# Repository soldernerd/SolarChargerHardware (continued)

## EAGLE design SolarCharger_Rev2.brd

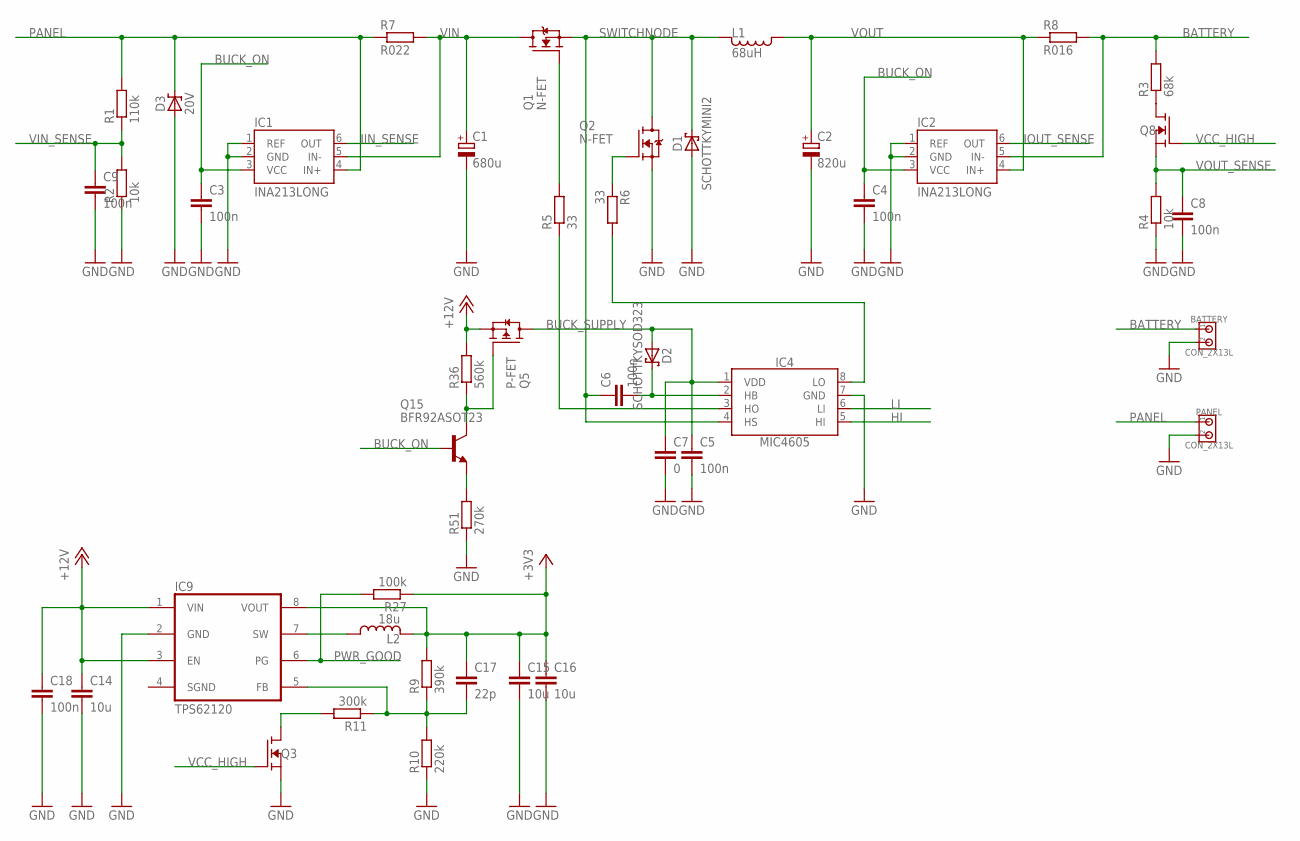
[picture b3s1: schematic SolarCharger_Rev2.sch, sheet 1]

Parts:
BATTERY: CON_2X13L; 200MIL_2X
C1: 680u; 10MM
C2: 820u; 10MM
C3, C4, C5, C6, C8, C9: 100n; C0805
C7: 0; C0805
C14: 10u; C1206
C15, C16: 10u; C0805
C17: 22p; C0805
C18: 100n; C1206
D1: SCHOTTKYMINI2; MINI2-F3-B
D2: SCHOTTKYSOD323; SOD323
D3: 20V; SMC
IC1, IC2: INA213LONG; SC70-6_LONG
IC4: MIC4605; SOIC8
IC9: TPS62120; SOT-23-8
L1: 68uH; MSS1583
L2: 18u; LPS3015
PANEL: CON_2X13L; 200MIL_2X
Q1, Q2: N-FET; TO263-3
Q3, Q8: N-FETSOT23; SOT23
Q5: P-FET; SOT23
Q15: BFR92ASOT23; SOT23
R1: 110k; R0805
R2, R4: 10k; R0805
R3: 68k; R0805
R5, R6: 33; R0805
R7: R022; 0612
R8: R016; 0612
R9: 390k; R0805
R10: 220k; R0805
R11: 300k; R0805
R27: 100k; R0805
R36: 560k; R0805
R51: 270k; R0805

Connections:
BATTERY: BATTERY.1, IC2.5 (IN-), R3.2, R8.2; also elsewhere on the board
BUCK_ON: C3.1, C4.1, IC1.3 (VCC), IC2.3 (VCC), Q15.1 (B); also elsewhere on the board
BUCK_SUPPLY: C5.1, C7.1, D2.A, IC4.1 (VDD), Q5.3 (D)
GND: BATTERY.2, C1.-, C2.-, C3.2, C4.2, C5.2, C7.2, C8.2, C9.2, C14.2, C15.2, C16.2, C18.2, D1.A, D3.A, IC1.1 (REF), IC1.2 (GND), IC2.1 (REF), IC2.2 (GND), IC4.7 (GND), IC9.2 (GND), PANEL.2, Q2.3 (S), Q3.2 (S), R2.1, R4.1, R10.1, R51.1; also elsewhere on the board
HI: IC4.5 (HI); also elsewhere on the board
IIN_SENSE: IC1.6 (OUT); also elsewhere on the board
IOUT_SENSE: IC2.6 (OUT); also elsewhere on the board
LI: IC4.6 (LI); also elsewhere on the board
unnamed: C6.2, D2.C, IC4.2 (HB)
unnamed: Q1.1 (G), R5.2
unnamed: Q3.3 (D), R11.2
unnamed: Q2.1 (G), R6.1
unnamed: IC4.8 (LO), R6.2
unnamed: IC9.7 (SW), L2.1
unnamed: C17.2, IC9.5 (FB), R9.1, R10.2, R11.1
unnamed: IC4.3 (HO), R5.1
unnamed: Q5.1 (G), Q15.3 (C), R36.1
unnamed: Q8.3 (D), R3.1
unnamed: Q15.2 (E), R51.2
PANEL: D3.C, IC1.4 (IN+), PANEL.1, R1.2, R7.1
PWR_GOOD: IC9.6 (PG), R27.2; also elsewhere on the board
SWITCHNODE: C6.1, D1.C, IC4.4 (HS), L1.2, Q1.3 (S), Q2.TAB (D)
VCC: C15.1, C16.1, C17.1, IC9.8 (VOUT), L2.2, R9.2, R27.1; also elsewhere on the board
VCC_HIGH: Q3.1 (G), Q8.1 (G); also elsewhere on the board
VIN: C1.+, IC1.5 (IN-), Q1.TAB (D), R7.2
VIN_SENSE: C9.1, R1.1, R2.2; also elsewhere on the board
VOUT: C2.+, C14.1, C18.1, IC2.4 (IN+), IC9.1 (VIN), IC9.3 (EN), L1.1, Q5.2 (S), R8.1, R36.2; also elsewhere on the board
VOUT_SENSE: C8.1, Q8.2 (S), R4.2; also elsewhere on the board

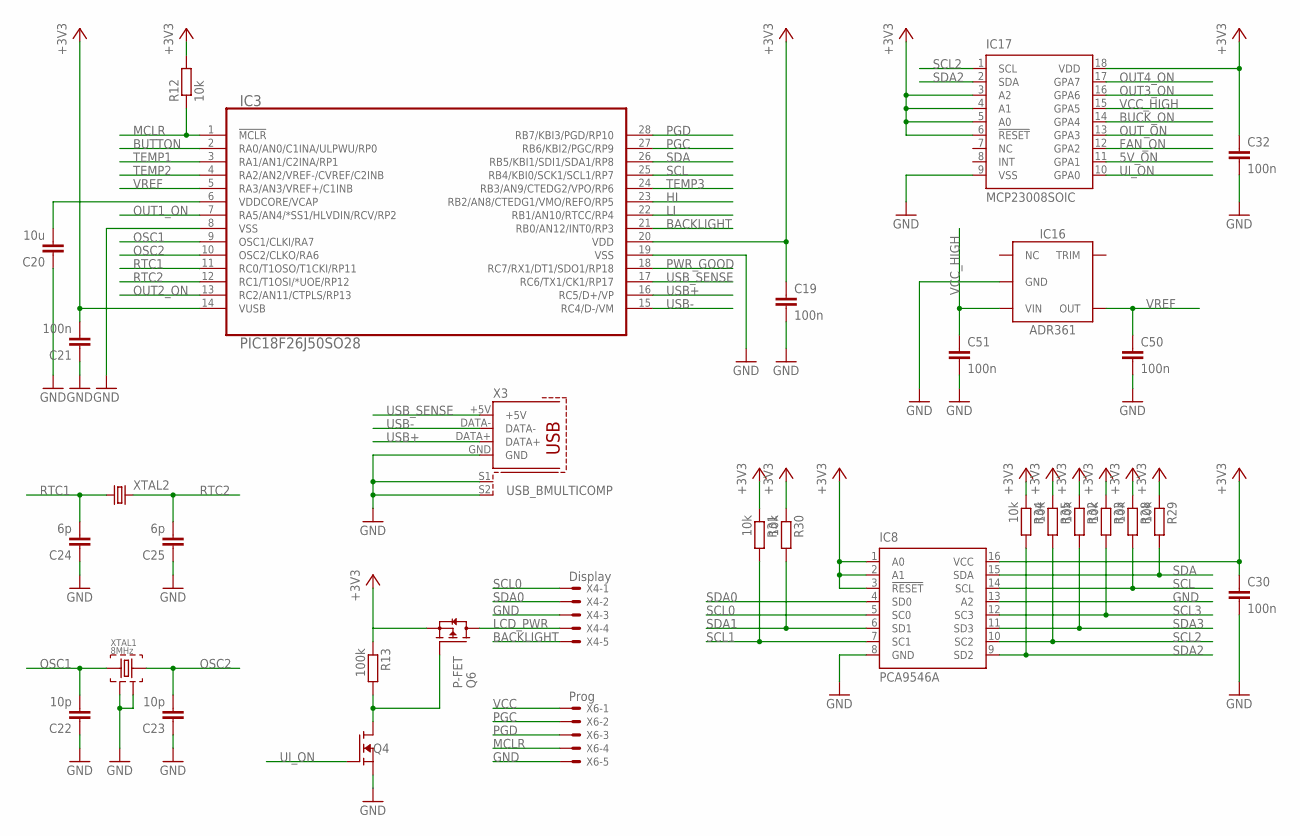
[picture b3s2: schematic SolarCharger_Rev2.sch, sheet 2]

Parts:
C19, C21, C30, C32, C50, C51: 100n; C0805
C20: 10u; C0805
C22, C23: 10p; C0805
C24, C25: 6p; C0805
IC3: PIC18F26J50SO28; SO28W
IC8: PCA9546A; SO16
IC16: ADR361; SOT23-5
IC17: MCP23008SOIC; SO18W
Q4: N-FETSOT23; SOT23
Q6: P-FET; SOT23
R12, R28, R29, R30, R31, R32, R33, R34, R35: 10k; R0805
R13: 100k; R0805
X3: USB_BMULTICOMP; USB_B
X4: Display; 22-23-2051
X6: Prog; 22-23-2051
XTAL1: 8MHz; 5X3.2MM
XTAL2: CRYSTAL3.2X1.5; 3.2X1.5MM

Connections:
5V_ON: IC17.11 (GPA1); also elsewhere on the board
BACKLIGHT: IC3.21 (RB0/AN12/INT0/RP3), X4.5
BUCK_ON: IC17.14 (GPA4); also elsewhere on the board
BUTTON: IC3.2 (RA0/AN0/C1INA/ULPWU/RP0); also elsewhere on the board
FAN_ON: IC17.12 (GPA2); also elsewhere on the board
GND: C19.2, C20.1, C21.1, C22.1, C23.1, C24.1, C25.1, C30.2, C32.2, C50.2, C51.2, IC3.8 (VSS), IC3.19 (VSS), IC8.8 (GND), IC8.13 (A2), IC16.2 (GND), IC17.9 (VSS), Q4.2 (S), X3.GND, X3.S1, X3.S2, X4.3, X6.5, XTAL1.2, XTAL1.4; also elsewhere on the board
HI: IC3.23 (RB2/AN8/CTEDG1/VMO/REFO/RP5); also elsewhere on the board
LCD_PWR: Q6.3 (D), X4.4
LI: IC3.22 (RB1/AN10/RTCC/RP4); also elsewhere on the board
MCLR: IC3.1 (!MCLR!), R12.1, X6.4
unnamed: Q4.3 (D), Q6.1 (G), R13.2
unnamed: C20.2, IC3.6 (VDDCORE/VCAP)
OSC1: C22.2, IC3.9 (OSC1/CLKI/RA7), XTAL1.1
OSC2: C23.2, IC3.10 (OSC2/CLKO/RA6), XTAL1.3
OUT1_ON: IC3.7 (RA5/AN4/*SS1/HLVDIN/RCV/RP2); also elsewhere on the board
OUT2_ON: IC3.13 (RC2/AN11/CTPLS/RP13); also elsewhere on the board
OUT3_ON: IC17.16 (GPA6); also elsewhere on the board
OUT4_ON: IC17.17 (GPA7); also elsewhere on the board
OUT_ON: IC17.13 (GPA3); also elsewhere on the board
PGC: IC3.27 (RB6/KBI2/PGC/RP9), X6.2; also elsewhere on the board
PGD: IC3.28 (RB7/KBI3/PGD/RP10), X6.3; also elsewhere on the board
PWR_GOOD: IC3.18 (RC7/RX1/DT1/SDO1/RP18); also elsewhere on the board
RTC1: C24.2, IC3.11 (RC0/T1OSO/T1CKI/RP11), XTAL2.1
RTC2: C25.2, IC3.12 (RC1/T1OSI/*UOE/RP12), XTAL2.2
SCL: IC3.25 (RB4/KBI0/SCK1/SCL1/RP7), IC8.14 (SCL), R28.2
SCL0: IC8.5 (SC0), X4.1
SCL1: IC8.7 (SC1), R31.2; also elsewhere on the board
SCL2: IC8.10 (SC2), IC17.1 (SCL), R35.2
SCL3: IC8.12 (SC3), R33.2; also elsewhere on the board
SDA: IC3.26 (RB5/KBI1/SDI1/SDA1/RP8), IC8.15 (SDA), R29.2
SDA0: IC8.4 (SD0), X4.2
SDA1: IC8.6 (SD1), R30.2; also elsewhere on the board
SDA2: IC8.9 (SD2), IC17.2 (SDA), R34.2
SDA3: IC8.11 (SD3), R32.2; also elsewhere on the board
TEMP1: IC3.3 (RA1/AN1/C2INA/RP1); also elsewhere on the board
TEMP2: IC3.4 (RA2/AN2/VREF-/CVREF/C2INB); also elsewhere on the board
TEMP3: IC3.24 (RB3/AN9/CTEDG2/VPO/RP6); also elsewhere on the board
UI_ON: IC17.10 (GPA0), Q4.1 (G); also elsewhere on the board
USB+: IC3.16 (RC5/D+/VP), X3.DATA+
USB-: IC3.15 (RC4/D-/VM), X3.DATA-
USB_SENSE: IC3.17 (RC6/TX1/CK1/RP17), X3.+5V
VCC: C19.1, C21.2, C30.1, C32.1, IC3.14 (VUSB), IC3.20 (VDD), IC8.1 (A0), IC8.2 (A1), IC8.3 (!RESET!), IC8.16 (VCC), IC17.3 (A2), IC17.4 (A1), IC17.5 (A0), IC17.6 (!RESET), IC17.18 (VDD), Q6.2 (S), R12.2, R13.1, R28.1, R29.1, R30.1, R31.1, R32.1, R33.1, R34.1, R35.1, X6.1; also elsewhere on the board
VCC_HIGH: C51.1, IC16.3 (VIN), IC17.15 (GPA5); also elsewhere on the board
VREF: C50.1, IC3.5 (RA3/AN3/VREF+/C1INB), IC16.4 (OUT)

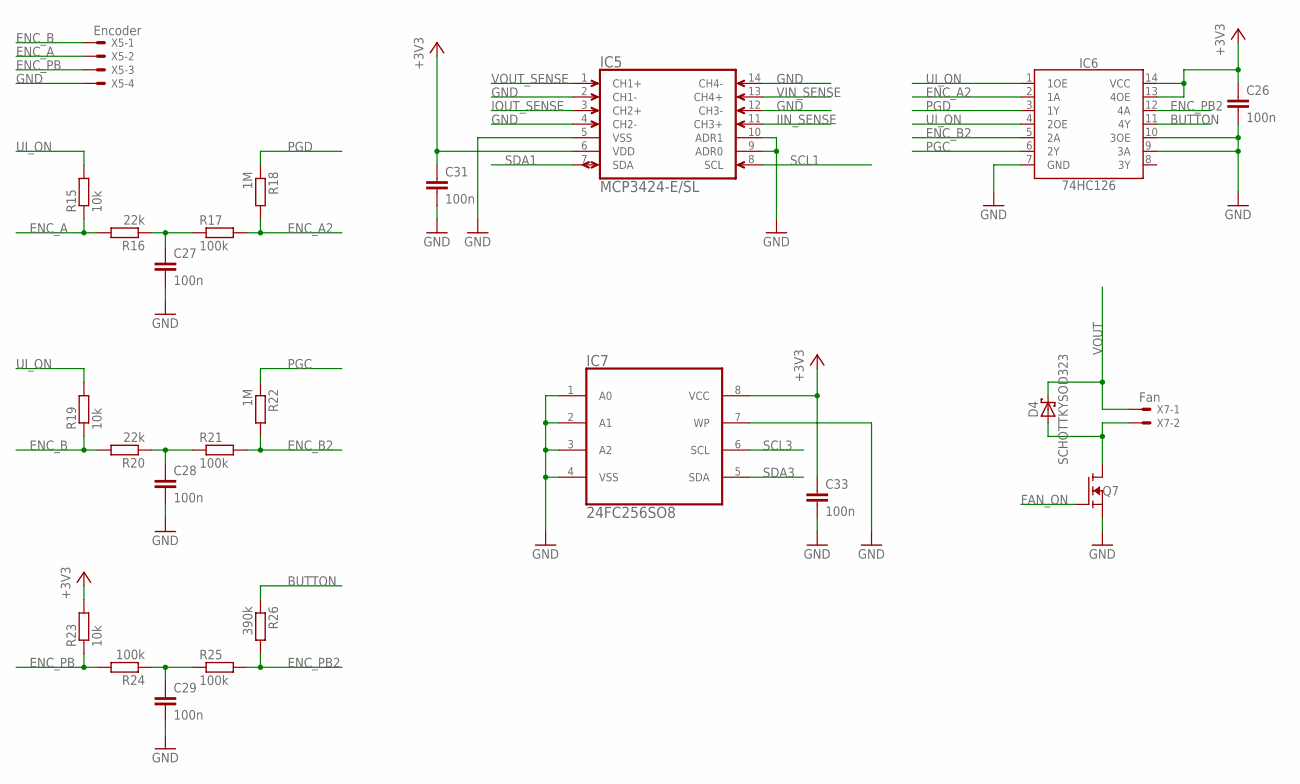
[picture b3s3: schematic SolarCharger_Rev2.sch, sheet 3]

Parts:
C26, C27, C28, C29, C31, C33: 100n; C0805
D4: SCHOTTKYSOD323; SOD323
IC5: MCP3424-E/SL; SOIC14
IC6: 74HC126; SO14
IC7: 24FC256SO8; SOIC8
Q7: N-FETSOT23; SOT23
R15, R19, R23: 10k; R0805
R16, R20: 22k; R0805
R17, R21, R24, R25: 100k; R0805
R18, R22: 1M; R0805
R26: 390k; R0805
X5: Encoder; 22-23-2041
X7: Fan; 22-23-2021

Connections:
BUTTON: IC6.11 (4Y), R26.1; also elsewhere on the board
ENC_A: R15.1, R16.2, X5.2
ENC_A2: IC6.2 (1A), R17.2, R18.2
ENC_B: R19.1, R20.2, X5.1
ENC_B2: IC6.5 (2A), R21.2, R22.2
ENC_PB: R23.1, R24.2, X5.3
ENC_PB2: IC6.12 (4A), R25.2, R26.2
FAN_ON: Q7.1 (G); also elsewhere on the board
GND: C26.2, C27.2, C28.2, C29.2, C31.2, C33.2, IC5.2 (CH1-), IC5.4 (CH2-), IC5.5 (VSS), IC5.9 (ADR0), IC5.10 (ADR1), IC5.12 (CH3-), IC5.14 (CH4-), IC6.7 (GND), IC6.9 (3A), IC6.10 (3OE), IC7.1 (A0), IC7.2 (A1), IC7.3 (A2), IC7.4 (VSS), IC7.7 (WP), Q7.2 (S), X5.4; also elsewhere on the board
IIN_SENSE: IC5.11 (CH3+); also elsewhere on the board
IOUT_SENSE: IC5.3 (CH2+); also elsewhere on the board
unnamed: C28.1, R20.1, R21.1
unnamed: D4.A, Q7.3 (D), X7.2
unnamed: C27.1, R16.1, R17.1
unnamed: C29.1, R24.1, R25.1
PGC: IC6.6 (2Y), R22.1; also elsewhere on the board
PGD: IC6.3 (1Y), R18.1; also elsewhere on the board
SCL1: IC5.8 (SCL); also elsewhere on the board
SCL3: IC7.6 (SCL); also elsewhere on the board
SDA1: IC5.7 (SDA); also elsewhere on the board
SDA3: IC7.5 (SDA); also elsewhere on the board
UI_ON: IC6.1 (1OE), IC6.4 (2OE), R15.2, R19.2; also elsewhere on the board
VCC: C26.1, C31.1, C33.1, IC5.6 (VDD), IC6.13 (4OE), IC6.14 (VCC), IC7.8 (VCC), R23.2; also elsewhere on the board
VIN_SENSE: IC5.13 (CH4+); also elsewhere on the board
VOUT: D4.C, X7.1; also elsewhere on the board
VOUT_SENSE: IC5.1 (CH1+); also elsewhere on the board

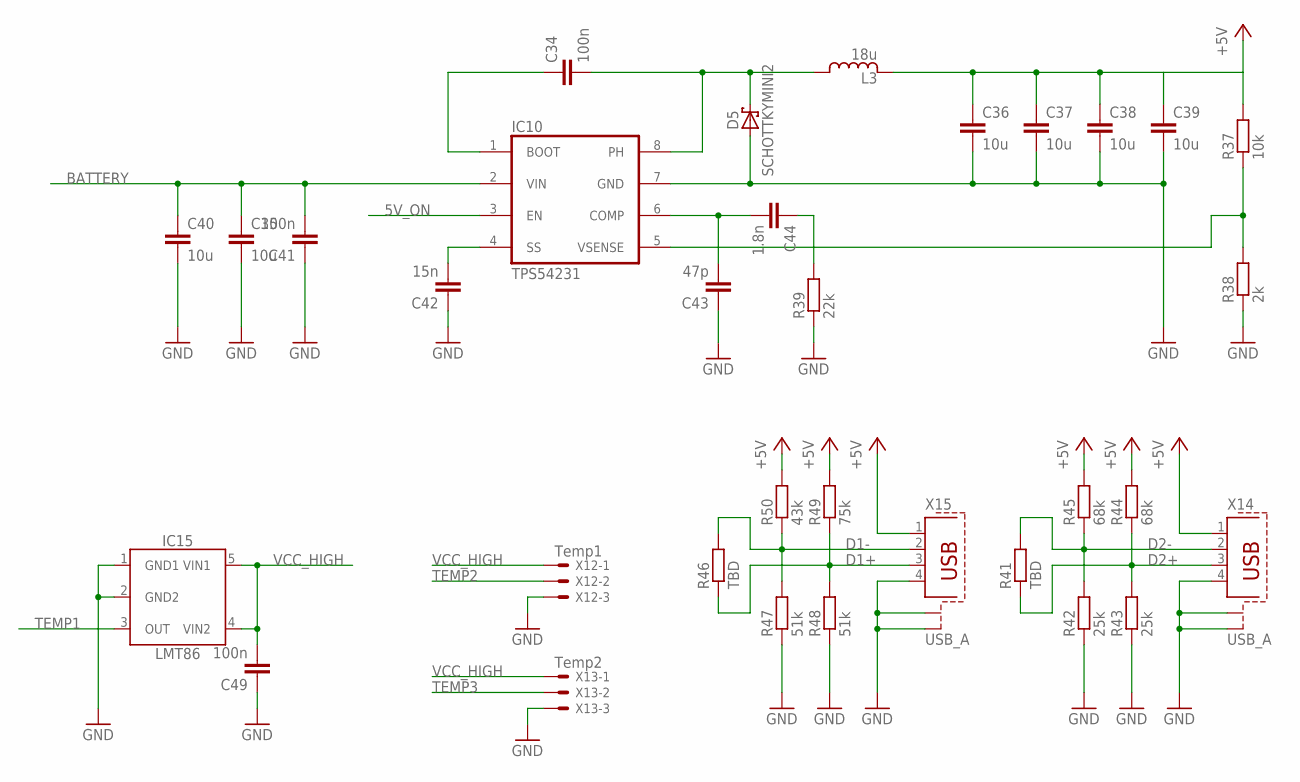
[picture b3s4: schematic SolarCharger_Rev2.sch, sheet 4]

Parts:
C34, C41, C49: 100n; C0805
C35, C36, C37, C38, C39, C40: 10u; C1206
C42: 15n; C0805
C43: 47p; C0805
C44: 1.8n; C0805
D5: SCHOTTKYMINI2; MINI2-F3-B
IC10: TPS54231; SO8
IC15: LMT86; SC70-5
L3: 18u; MSS1038
R37: 10k; R0805
R38: 2k; R0805
R39: 22k; R0805
R41, R46: TBD; R0805
R42, R43: 25k; R0805
R44, R45: 68k; R0805
R47, R48: 51k; R0805
R49: 75k; R0805
R50: 43k; R0805
X12: Temp1; 22-23-2031
X13: Temp2; 22-23-2031
X14, X15: USB_A

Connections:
5V_ON: IC10.3 (EN); also elsewhere on the board
+5V: C36.1, C37.1, C38.1, C39.1, L3.2, R37.2, R44.2, R45.2, R49.2, R50.2, X14.1, X15.1
BATTERY: C35.1, C40.1, C41.2, IC10.2 (VIN); also elsewhere on the board
D1+: R46.1, R48.2, R49.1, X15.3
D1-: R46.2, R47.2, R50.1, X15.2
D2+: R41.1, R43.2, R44.1, X14.3
D2-: R41.2, R42.2, R45.1, X14.2
GND: C35.2, C36.2, C37.2, C38.2, C39.2, C40.2, C41.1, C42.1, C43.1, C49.1, D5.A, IC10.7 (GND), IC15.1 (GND1), IC15.2 (GND2), R38.1, R39.1, R42.1, R43.1, R47.1, R48.1, X12.3, X13.3, X14.4, X14.S1, X14.S2, X15.4, X15.S1, X15.S2; also elsewhere on the board
unnamed: C34.1, IC10.1 (BOOT)
unnamed: C42.2, IC10.4 (SS)
unnamed: C34.2, D5.C, IC10.8 (PH), L3.1
unnamed: IC10.5 (VSENSE), R37.1, R38.2
unnamed: C44.1, R39.2
unnamed: C43.2, C44.2, IC10.6 (COMP)
TEMP1: IC15.3 (OUT); also elsewhere on the board
TEMP2: X12.2; also elsewhere on the board
TEMP3: X13.2; also elsewhere on the board
VCC_HIGH: C49.2, IC15.4 (VIN2), IC15.5 (VIN1), X12.1, X13.1; also elsewhere on the board

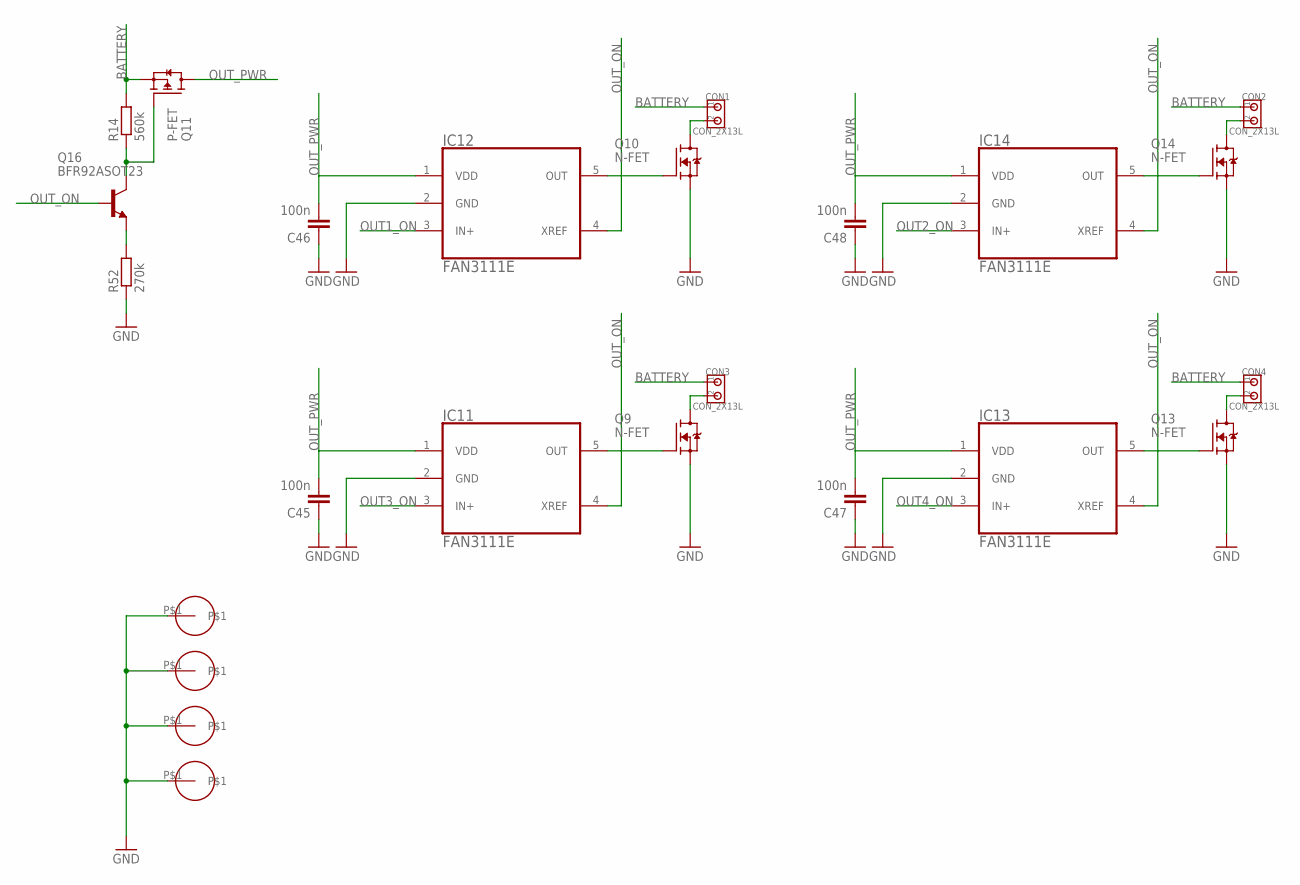
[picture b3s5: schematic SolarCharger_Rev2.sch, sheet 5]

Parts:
C45, C46, C47, C48: 100n; C0805
CON1, CON2, CON3, CON4: CON_2X13L; 200MIL_2X
IC11, IC12, IC13, IC14: FAN3111E; SOT-23-5
Q9, Q10, Q13, Q14: N-FET; TO263-3
Q11: P-FET; SOT23
Q16: BFR92ASOT23; SOT23
R14: 560k; R0805
R52: 270k; R0805
U$1, U$2, U$3, U$4: HOLE_3.3MM

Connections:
BATTERY: CON1.1, CON2.1, CON3.1, CON4.1, Q11.2 (S), R14.2; also elsewhere on the board
GND: C45.1, C46.1, C47.1, C48.1, IC11.2 (GND), IC12.2 (GND), IC13.2 (GND), IC14.2 (GND), Q9.3 (S), Q10.3 (S), Q13.3 (S), Q14.3 (S), R52.1, U$1.P$1, U$2.P$1, U$3.P$1, U$4.P$1; also elsewhere on the board
unnamed: Q11.1 (G), Q16.3 (C), R14.1
unnamed: CON3.2, Q9.TAB (D)
unnamed: IC11.5 (OUT), Q9.1 (G)
unnamed: CON1.2, Q10.TAB (D)
unnamed: IC12.5 (OUT), Q10.1 (G)
unnamed: CON4.2, Q13.TAB (D)
unnamed: IC13.5 (OUT), Q13.1 (G)
unnamed: CON2.2, Q14.TAB (D)
unnamed: IC14.5 (OUT), Q14.1 (G)
unnamed: Q16.2 (E), R52.2
OUT1_ON: IC12.3 (IN+); also elsewhere on the board
OUT2_ON: IC14.3 (IN+); also elsewhere on the board
OUT3_ON: IC11.3 (IN+); also elsewhere on the board
OUT4_ON: IC13.3 (IN+); also elsewhere on the board
OUT_ON: IC11.4 (XREF), IC12.4 (XREF), IC13.4 (XREF), IC14.4 (XREF), Q16.1 (B); also elsewhere on the board
OUT_PWR: C45.2, C46.2, C47.2, C48.2, IC11.1 (VDD), IC12.1 (VDD), IC13.1 (VDD), IC14.1 (VDD), Q11.3 (D)

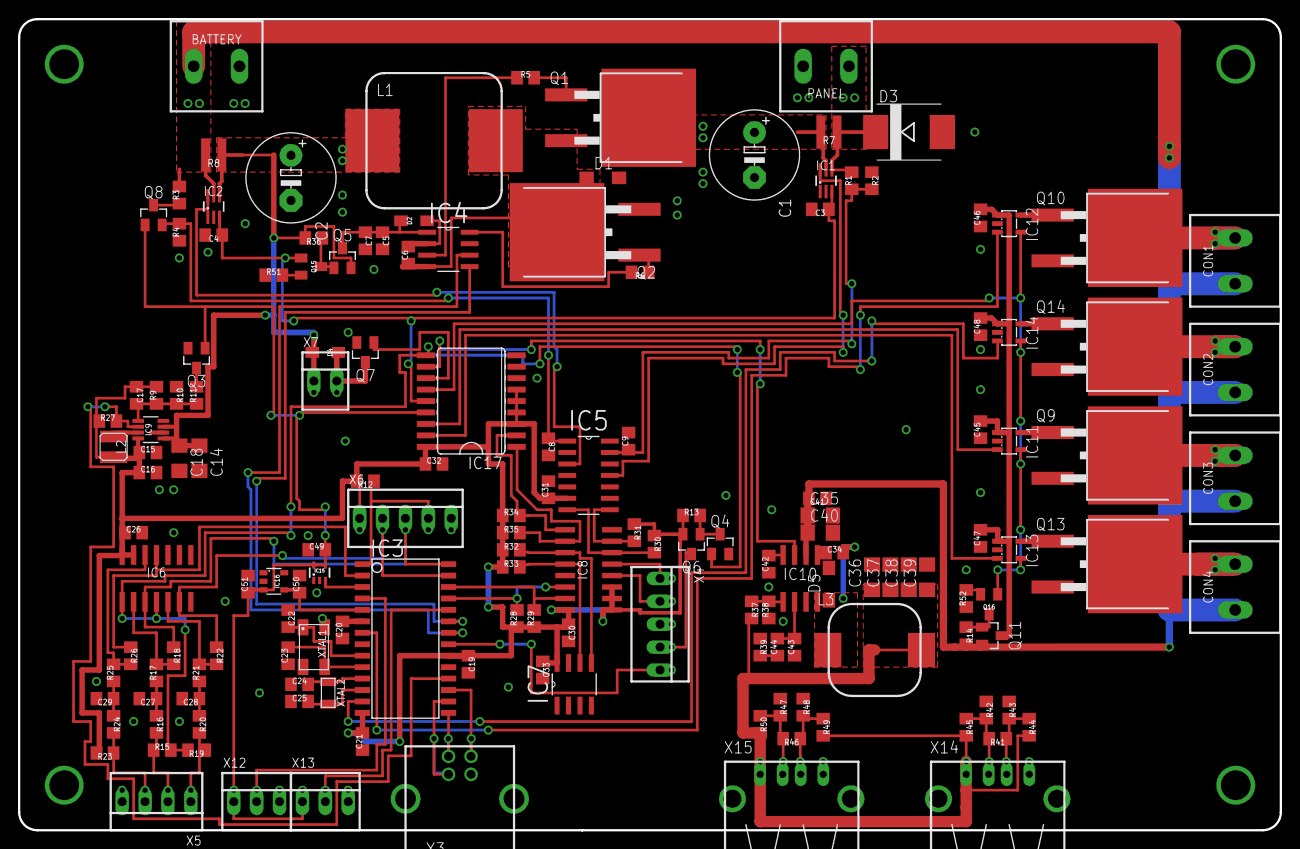
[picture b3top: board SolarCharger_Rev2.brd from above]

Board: 2 copper layers, 140.0 x 90.0 mm, 159 parts (0 on the bottom side), 97 nets.

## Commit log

2017-03-18 Some resistor values fixed
2017-06-06 Some resistor values changed
2017-09-04 Revision D completed
2017-09-11 Power supply for high voltage version more or less final. Schematics only, no layout yet.
2017-09-14 Buck for high voltage version nearly completed. Mosfet footprint still to be changed. Low-side current sensing implemented
2017-10-28 Flash now supplied directly from VCC
2018-01-01 Revision E completed. Now with SPI and I2C headers
2018-01-01 Some ground connections improved
2018-01-02 Some final minor changes. Moved a capacitor, re-routed a VCC trace. Gerbers exported as ordered
2018-01-07 Rev F files added. Switched pins for FAN_OUT and SS2
2018-02-18 Revision F: Just swapped 2 signals
2018-06-25 Slightly modified the board (but noch schematics) of the Arduino version. The new version is intended for a professionally etched board with plated through vias, silkscreen and all.
